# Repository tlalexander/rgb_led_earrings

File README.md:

# rgb_led_earrings

CAD:
https://cad.onshape.com/documents/09024334f2a397aa5bc58e5a/w/46f4970e419c9b5834fa8bd0/e/3dd3a53ca6818e1934df52f5

A gentle glow shines from your direction.
A twist, a step, a shimmy.
You move with freedom in your space.
Today is a good day. <3

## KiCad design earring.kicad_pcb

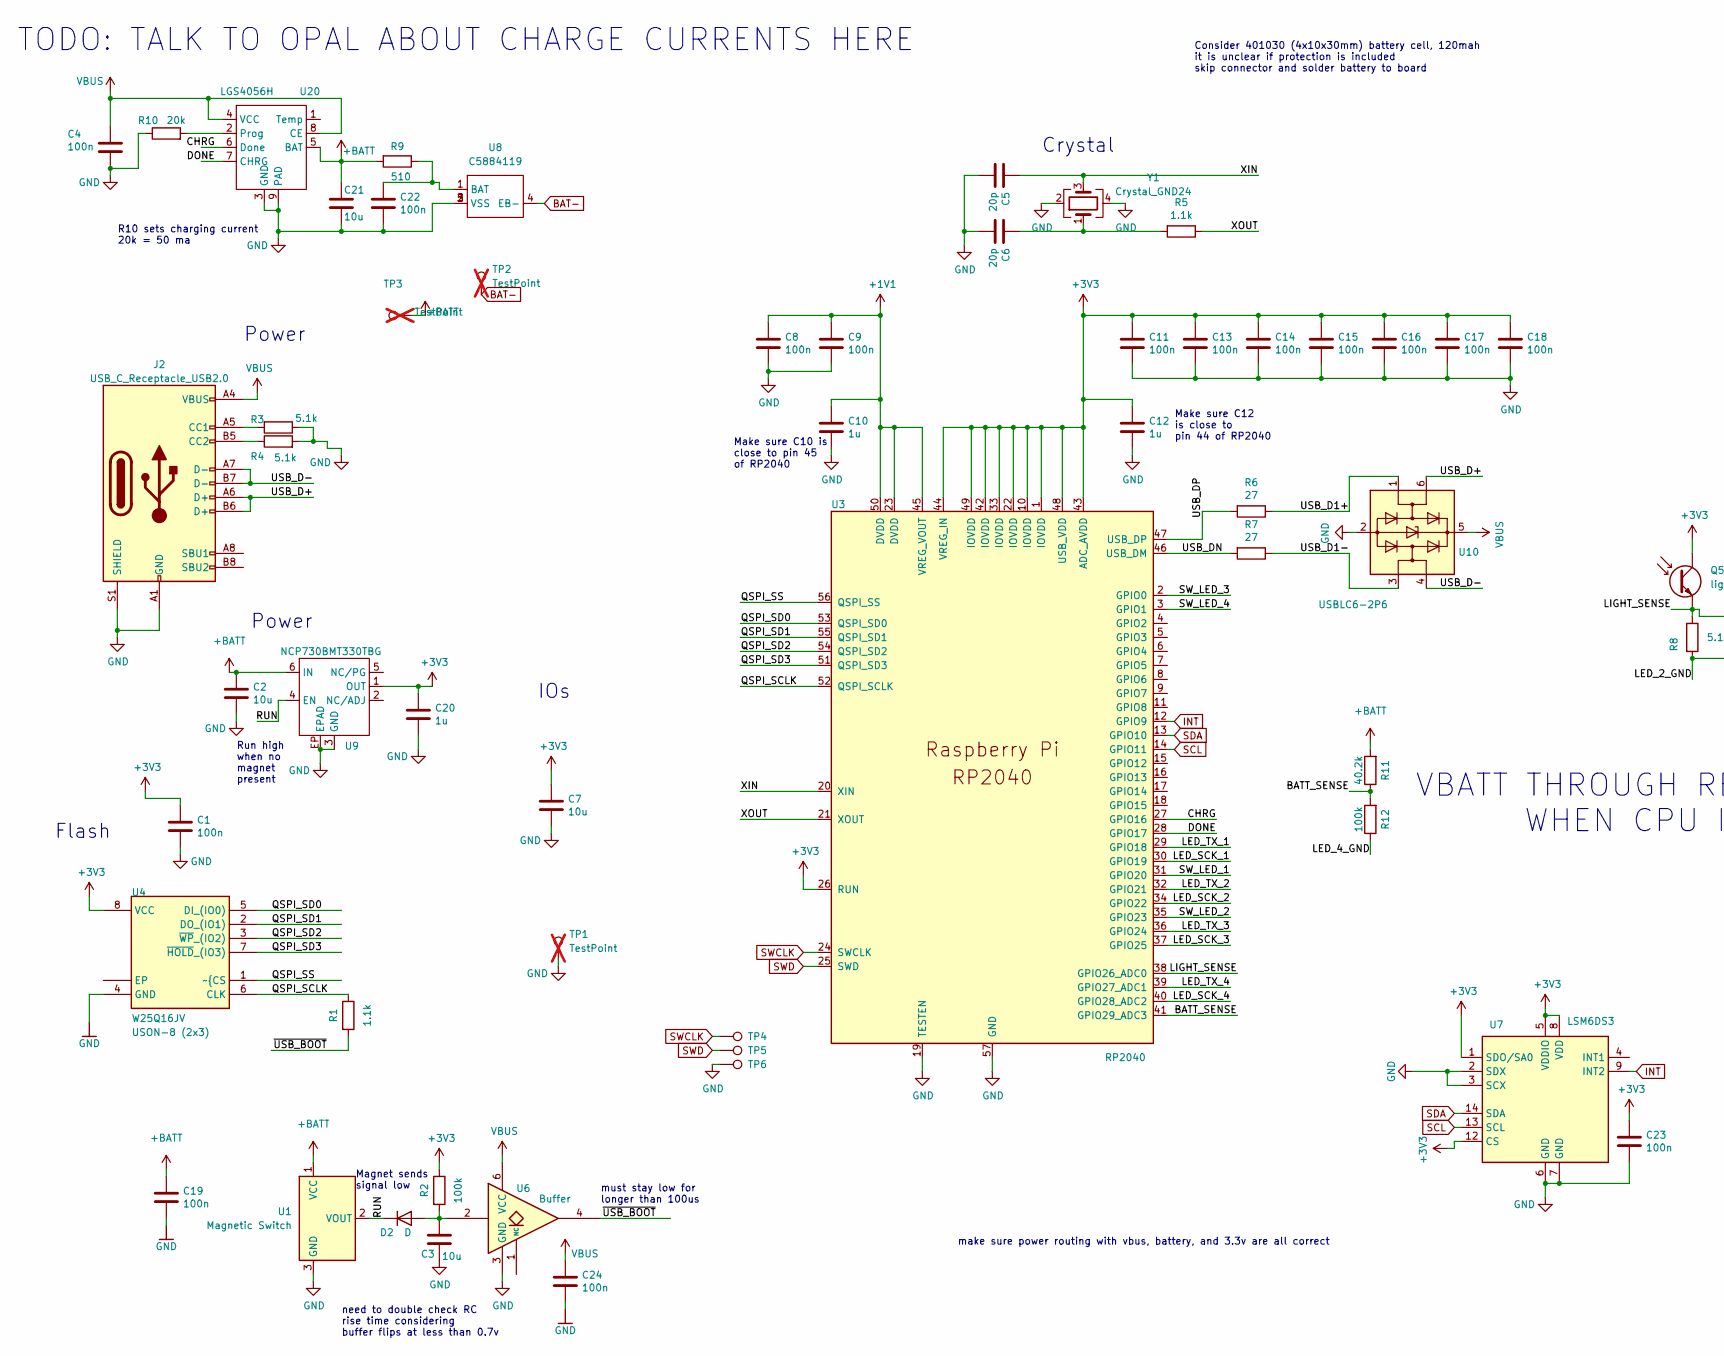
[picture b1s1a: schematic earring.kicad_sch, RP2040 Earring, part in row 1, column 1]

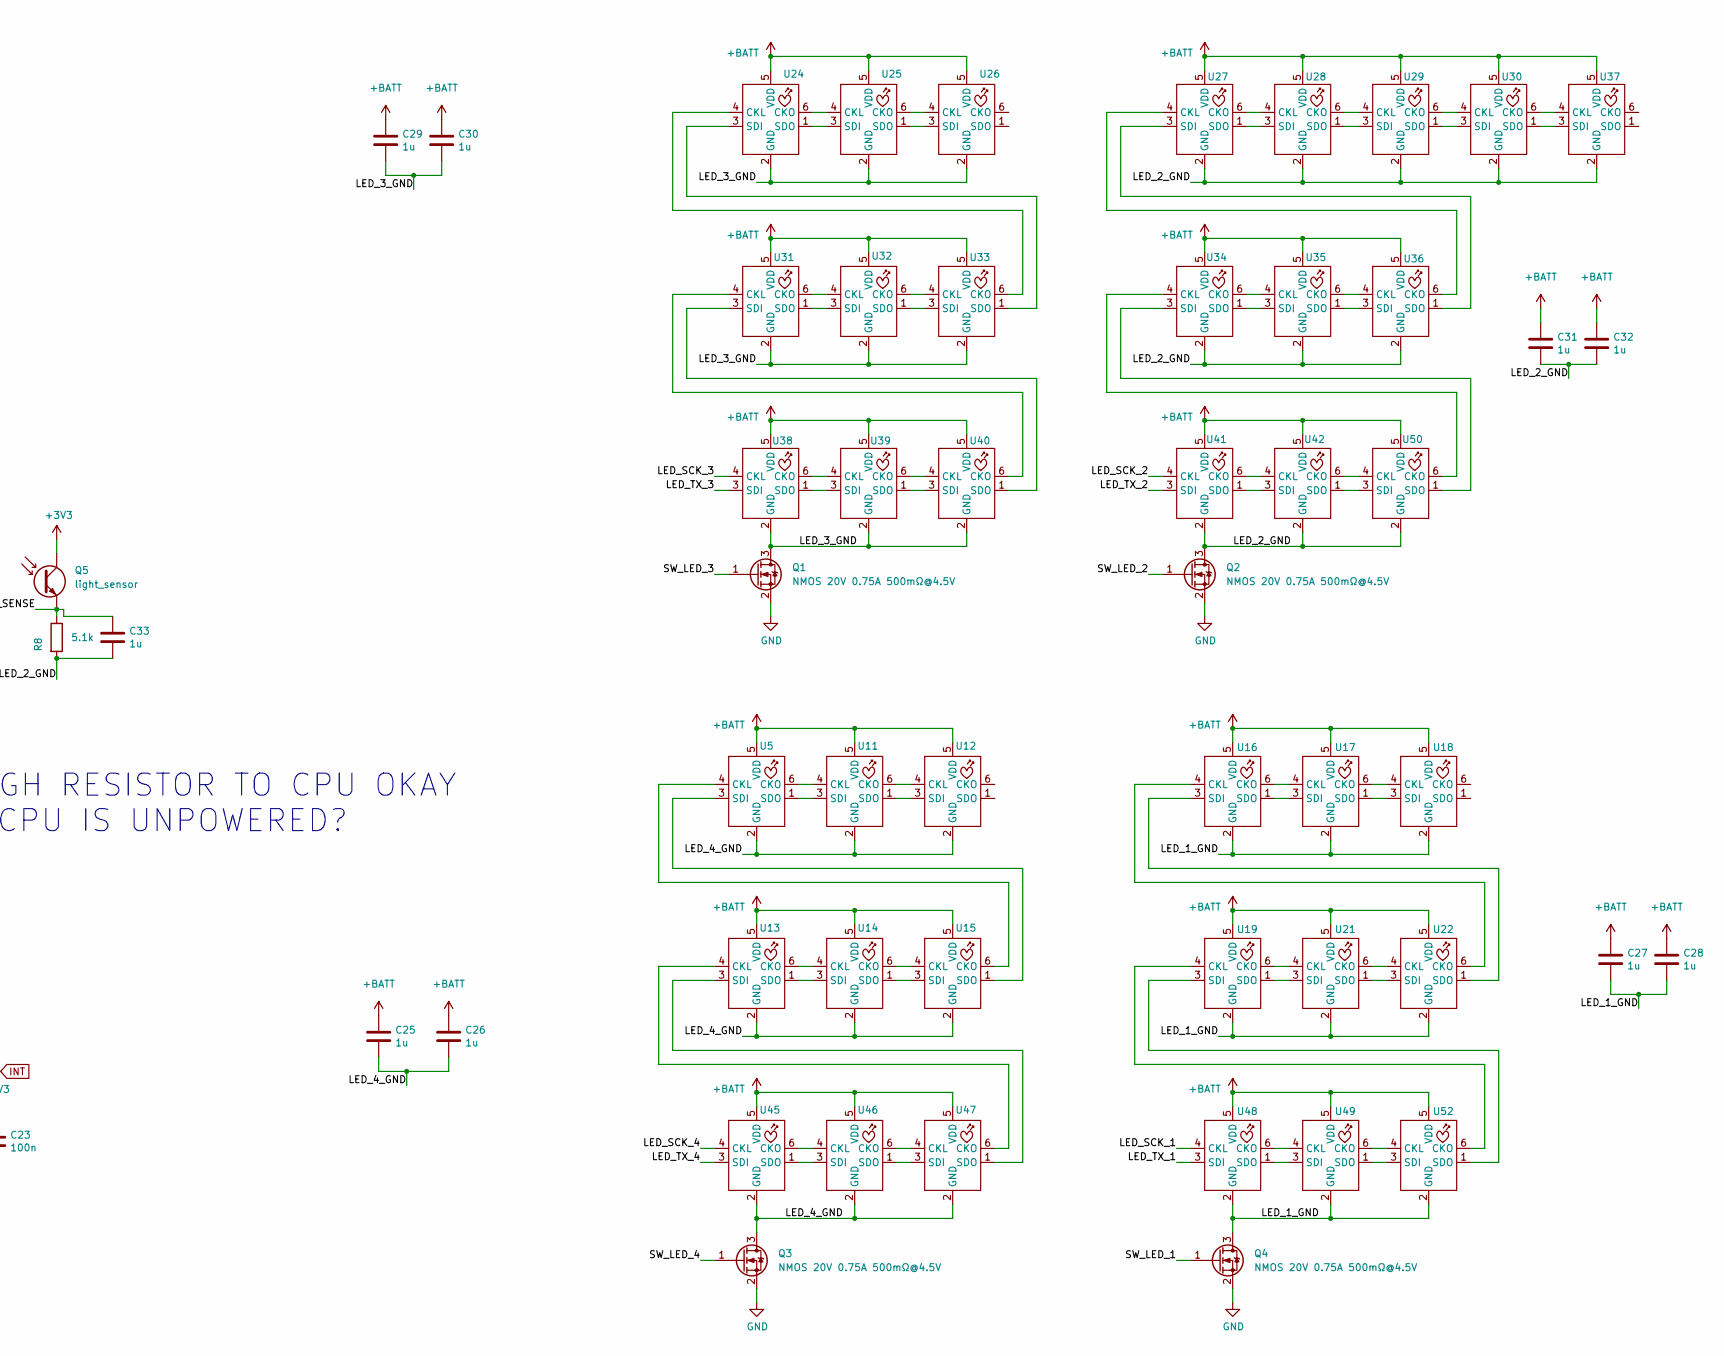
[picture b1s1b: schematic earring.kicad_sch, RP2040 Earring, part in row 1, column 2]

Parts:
C1, C4, C8, C9, C11, C13, C14, C15, C16, C17, C18, C19, C22, C23, C24: 100n; C_0402_1005Metric; LCSC C60474
C2, C3, C7, C21: 10u; C_0402_1005Metric; LCSC C315248
C5, C6: 20p; C_0402_1005Metric; LCSC C107000
C10, C12, C20, C25, C26, C27, C28, C29, C30, C31, C32, C33: 1u; C_0402_1005Metric; LCSC C29266
D2: D; D_SOD-523; LCSC C4468063
J2: USB_C_Receptacle_USB2.0; USB-C-TH_GT-USB-7055; LCSC C2686963
Q1, Q2, Q3, Q4: NMOS 20V 0.75A 500mΩ@4.5V; Diodes_DFN1006-3; LCSC C504098
Q5: light_sensor; LED_0603_1608Metric; LCSC C146233
R1, R5: 1.1k; R_0402_1005Metric; LCSC C325543
R2, R12: 100k; R_0402_1005Metric; LCSC C60491
R3, R4, R8: 5.1k; R_0402_1005Metric; LCSC C25905
R6, R7: 27; R_0402_1005Metric; LCSC C138021
R9: 510; R_0402_1005Metric; LCSC C137860
R10: 20k; R_0402_1005Metric; LCSC C25765
R11: 40.2k; R_0402_1005Metric; LCSC C25893
TP1: TestPoint; TestPoint_Pad_D1.0mm; LCSC C238130; not fitted
TP2, TP3: TestPoint; TestPoint_Pad_2.0x2.0mm; LCSC C238130; not fitted
TP4, TP5, TP6: TestPoint; TestPoint_Pad_1.0x1.0mm
U1: Magnetic Switch; DFN1608-3_L1.5-W0.8-P0.42-BL-EP; LCSC C879626
U3: RP2040; RP2040-QFN-56; LCSC C2040
U4: W25Q16JV; IC_W25Q16JVUXIQ_TR; MPN W25Q16JVUXIQ; LCSC C2843335
U5, U11, U12, U13, U14, U15, U16, U17, U18, U19, U21, U22, U25, U26, U27, U28, U29, U30, U31, U32, U33, U34, U35, U36, U37, U38, U39, U40, U41, U42, U45, U46, U47, U48, U49, U50, U52: LED-SK9822-EC20
U6: Buffer; UFDFN-6_1.45x1mm; LCSC C2864615
U7: LSM6DS3; LGA-14_3x2.5mm_P0.5mm_LayoutBorder3x4y; LCSC C2829074
U8: DFN1x1; LCSC C5884119
U9: NCP730BMT330TBG; WDFN-6-2x2; LCSC C892821
U10: USBLC6-2P6; SOT-666; LCSC C2827693
U20: LGS4056H; DFN-8-1EP_2x2mm_P0.5mm_EP0.9x1.5mm; LCSC C5124109
U24: SK9822-EC20; LED-SK9822-EC20
Y1: Crystal_GND24; Crystal_SMD_2520-4Pin_2.5x2.0mm; LCSC C284155

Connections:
+1V1: C8.1, C9.1, C10.1, U3.23 (DVDD), U3.45 (VREG_VOUT), U3.50 (DVDD)
+3V3: C1.1, C7.1, C11.1, C12.1, C13.1, C14.1, C15.1, C16.1, C17.1, C18.1, C20.1, C23.1, Q5.1, R2.1, U3.1 (IOVDD), U3.10 (IOVDD), U3.22 (IOVDD), U3.26 (RUN), U3.33 (IOVDD), U3.42 (IOVDD), U3.43 (ADC_AVDD), U3.44 (VREG_IN), U3.48 (USB_VDD), U3.49 (IOVDD), U4.8 (VCC), U7.1 (SDO/SA0), U7.5 (VDDIO), U7.8 (VDD), U7.12 (CS), U9.1 (OUT)
+BATT: C2.1, C19.1, C21.1, C25.1, C26.1, C27.1, C28.1, C29.1, C30.1, C31.1, C32.1, R9.2, R11.2, TP3.1, U1.1 (VCC), U5.5 (VDD), U9.6 (IN), U11.5 (VDD), U12.5 (VDD), U13.5 (VDD), U14.5 (VDD), U15.5 (VDD), U16.5 (VDD), U17.5 (VDD), U18.5 (VDD), U19.5 (VDD), U20.5 (BAT), U21.5 (VDD), U22.5 (VDD), U24.5 (VDD), U25.5 (VDD), U26.5 (VDD), U27.5 (VDD), U28.5 (VDD), U29.5 (VDD), U30.5 (VDD), U31.5 (VDD), U32.5 (VDD), U33.5 (VDD), U34.5 (VDD), U35.5 (VDD), U36.5 (VDD), U37.5 (VDD), U38.5 (VDD), U39.5 (VDD), U40.5 (VDD), U41.5 (VDD), U42.5 (VDD), U45.5 (VDD), U46.5 (VDD), U47.5 (VDD), U48.5 (VDD), U49.5 (VDD), U50.5 (VDD), U52.5 (VDD)
/BATT_SENSE: R11.1, R12.2, U3.41 (GPIO29_ADC3)
/CHRG: U3.27 (GPIO16), U20.6 (Done)
/DONE: U3.28 (GPIO17), U20.7 (CHRG)
/LED_1_GND: C27.2, C28.2, Q4.3 (D), U16.2 (GND), U17.2 (GND), U18.2 (GND), U19.2 (GND), U21.2 (GND), U22.2 (GND), U48.2 (GND), U49.2 (GND), U52.2 (GND)
/LED_2_GND: C31.2, C32.2, C33.2, Q2.3 (D), R8.2, U27.2 (GND), U28.2 (GND), U29.2 (GND), U30.2 (GND), U34.2 (GND), U35.2 (GND), U36.2 (GND), U37.2 (GND), U41.2 (GND), U42.2 (GND), U50.2 (GND)
/LED_3_GND: C29.2, C30.2, Q1.3 (D), U24.2 (GND), U25.2 (GND), U26.2 (GND), U31.2 (GND), U32.2 (GND), U33.2 (GND), U38.2 (GND), U39.2 (GND), U40.2 (GND)
/LED_4_GND: C25.2, C26.2, Q3.3 (D), R12.1, U5.2 (GND), U11.2 (GND), U12.2 (GND), U13.2 (GND), U14.2 (GND), U15.2 (GND), U45.2 (GND), U46.2 (GND), U47.2 (GND)
/LED_SCK_1: U3.30 (GPIO19), U48.4 (CKL)
/LED_SCK_2: U3.34 (GPIO22), U41.4 (CKL)
/LED_SCK_3: U3.37 (GPIO25), U38.4 (CKL)
/LED_SCK_4: U3.40 (GPIO28_ADC2), U45.4 (CKL)
/LED_TX_1: U3.29 (GPIO18), U48.3 (SDI)
/LED_TX_2: U3.32 (GPIO21), U41.3 (SDI)
/LED_TX_3: U3.36 (GPIO24), U38.3 (SDI)
/LED_TX_4: U3.39 (GPIO27_ADC1), U45.3 (SDI)
/LIGHT_SENSE: C33.1, Q5.2, R8.1, U3.38 (GPIO26_ADC0)
/QSPI_SCLK: R1.1, U3.52 (QSPI_SCLK), U4.6 (CLK)
/QSPI_SD0: U3.53 (QSPI_SD0), U4.5 (DI_(IO0))
/QSPI_SD1: U3.55 (QSPI_SD1), U4.2 (DO_(IO1))
/QSPI_SD2: U3.54 (QSPI_SD2), U4.3 (~WP_(IO2))
/QSPI_SD3: U3.51 (QSPI_SD3), U4.7 (~HOLD_(IO3))
/QSPI_SS: U3.56 (QSPI_SS), U4.1 (~{CS)
/RUN: D2.1 (K), U1.2 (VOUT), U9.4 (EN)
/SW_LED_1: Q4.1 (G), U3.31 (GPIO20)
/SW_LED_2: Q2.1 (G), U3.35 (GPIO23)
/SW_LED_3: Q1.1 (G), U3.2 (GPIO0)
/SW_LED_4: Q3.1 (G), U3.3 (GPIO1)
/USB_D1+: R6.1, U10.1 (I/O1)
/USB_D1-: R7.1, U10.3 (I/O2)
/USB_D+: J2.A6 (D+), J2.B6 (D+), U10.6 (I/O1)
/USB_D-: J2.A7 (D-), J2.B7 (D-), U10.4 (I/O2)
/USB_DN: R7.2, U3.46 (USB_DM)
/USB_DP: R6.2, U3.47 (USB_DP)
/XIN: C5.1, U3.20 (XIN), Y1.3
/XOUT: R5.1, U3.21 (XOUT)
/~USB_BOOT: R1.2, U6.4
BAT-: TP2.1, U8.4 (EB-)
GND: C1.2, C2.2, C3.2, C4.2, C5.2, C6.2, C7.2, C8.2, C9.2, C10.2, C11.2, C12.2, C13.2, C14.2, C15.2, C16.2, C17.2, C18.2, C19.2, C20.2, C21.2, C22.2, C23.2, C24.2, J2.A1 (GND), J2.A12 (GND), J2.B1 (GND), J2.B12 (GND), J2.S1 (SHIELD), Q1.2 (S), Q2.2 (S), Q3.2 (S), Q4.2 (S), R3.1, R4.2, R10.1, TP1.1, TP6.1, U1.3 (GND), U3.19 (TESTEN), U3.57 (GND), U4.4 (GND), U6.3 (GND), U7.2 (SDX), U7.3 (SCX), U7.6 (GND), U7.7 (GND), U8.2 (VSS), U8.3 (VSS), U8.5 (VSS), U9.3 (GND), U9.EP (EPAD), U10.2 (GND), U20.3 (GND), U20.9 (PAD), Y1.2, Y1.4
INT: U3.12 (GPIO9), U7.9 (INT2)
unnamed: C6.1, R5.2, Y1.1
unnamed: C3.1, D2.2 (A), R2.2, U6.2
unnamed: J2.A5 (CC1), R3.2
unnamed: J2.B5 (CC2), R4.1
unnamed: C22.1, R9.1, U8.1 (BAT)
unnamed: U5.6 (CKO), U11.4 (CKL)
unnamed: U11.6 (CKO), U12.4 (CKL)
unnamed: U5.1 (SDO), U11.3 (SDI)
unnamed: U11.1 (SDO), U12.3 (SDI)
unnamed: U13.4 (CKL), U47.6 (CKO)
unnamed: U13.6 (CKO), U14.4 (CKL)
unnamed: U13.3 (SDI), U47.1 (SDO)
unnamed: U13.1 (SDO), U14.3 (SDI)
unnamed: U14.6 (CKO), U15.4 (CKL)
unnamed: U14.1 (SDO), U15.3 (SDI)
unnamed: U5.4 (CKL), U15.6 (CKO)
unnamed: U5.3 (SDI), U15.1 (SDO)
unnamed: U16.4 (CKL), U22.6 (CKO)
unnamed: U16.6 (CKO), U17.4 (CKL)
unnamed: U16.3 (SDI), U22.1 (SDO)
unnamed: U16.1 (SDO), U17.3 (SDI)
unnamed: U17.6 (CKO), U18.4 (CKL)
unnamed: U17.1 (SDO), U18.3 (SDI)
unnamed: U19.4 (CKL), U52.6 (CKO)
unnamed: U19.6 (CKO), U21.4 (CKL)
unnamed: U19.3 (SDI), U52.1 (SDO)
unnamed: U19.1 (SDO), U21.3 (SDI)
unnamed: R10.2, U20.2 (Prog)
unnamed: U21.6 (CKO), U22.4 (CKL)
unnamed: U21.1 (SDO), U22.3 (SDI)
unnamed: U24.4 (CKL), U33.6 (CKO)
unnamed: U24.6 (CKO), U25.4 (CKL)
unnamed: U24.3 (SDI), U33.1 (SDO)
unnamed: U24.1 (SDO), U25.3 (SDI)
unnamed: U25.6 (CKO), U26.4 (CKL)
unnamed: U25.1 (SDO), U26.3 (SDI)
unnamed: U27.4 (CKL), U36.6 (CKO)
unnamed: U27.6 (CKO), U28.4 (CKL)
unnamed: U27.3 (SDI), U36.1 (SDO)
unnamed: U27.1 (SDO), U28.3 (SDI)
unnamed: U28.6 (CKO), U29.4 (CKL)
unnamed: U28.1 (SDO), U29.3 (SDI)
unnamed: U29.6 (CKO), U30.4 (CKL)
unnamed: U29.1 (SDO), U30.3 (SDI)
unnamed: U30.6 (CKO), U37.4 (CKL)
unnamed: U30.1 (SDO), U37.3 (SDI)
unnamed: U31.4 (CKL), U40.6 (CKO)
unnamed: U31.6 (CKO), U32.4 (CKL)
unnamed: U31.3 (SDI), U40.1 (SDO)
unnamed: U31.1 (SDO), U32.3 (SDI)
unnamed: U32.6 (CKO), U33.4 (CKL)
unnamed: U32.1 (SDO), U33.3 (SDI)
unnamed: U34.4 (CKL), U50.6 (CKO)
unnamed: U34.6 (CKO), U35.4 (CKL)
unnamed: U34.3 (SDI), U50.1 (SDO)
unnamed: U34.1 (SDO), U35.3 (SDI)
unnamed: U35.6 (CKO), U36.4 (CKL)
unnamed: U35.1 (SDO), U36.3 (SDI)
unnamed: U38.6 (CKO), U39.4 (CKL)
unnamed: U38.1 (SDO), U39.3 (SDI)
unnamed: U39.6 (CKO), U40.4 (CKL)
unnamed: U39.1 (SDO), U40.3 (SDI)
unnamed: U41.6 (CKO), U42.4 (CKL)
unnamed: U41.1 (SDO), U42.3 (SDI)
unnamed: U42.6 (CKO), U50.4 (CKL)
unnamed: U42.1 (SDO), U50.3 (SDI)
unnamed: U45.6 (CKO), U46.4 (CKL)
unnamed: U45.1 (SDO), U46.3 (SDI)
unnamed: U46.6 (CKO), U47.4 (CKL)
unnamed: U46.1 (SDO), U47.3 (SDI)
unnamed: U48.6 (CKO), U49.4 (CKL)
unnamed: U48.1 (SDO), U49.3 (SDI)
unnamed: U49.6 (CKO), U52.4 (CKL)
unnamed: U49.1 (SDO), U52.3 (SDI)
SCL: U3.14 (GPIO11), U7.13 (SCL)
SDA: U3.13 (GPIO10), U7.14 (SDA)
SWCLK: TP4.1, U3.24 (SWCLK)
SWD: TP5.1, U3.25 (SWD)
VBUS: C4.1, C24.1, J2.A4 (VBUS), J2.A9 (VBUS), J2.B4 (VBUS), J2.B9 (VBUS), U6.6 (VCC), U10.5 (VBUS), U20.4 (VCC), U20.8 (CE)

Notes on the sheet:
Make sure C10 is close to pin 45 of RP2040
Consider 401030 (4x10x30mm) battery cell, 120mah it is unclear if protection is included skip connector and solder battery to board
Power
Crystal
R10 sets charging current 20k = 50 ma
need to double check RC rise time considering buffer flips at less than 0.7v
IOs
TODO: TALK TO OPAL ABOUT CHARGE CURRENTS HERE
must stay low for longer than 100us
VBATT THROUGH RESISTOR TO CPU OKAY WHEN CPU IS UNPOWERED?
Magnet sends signal low
Make sure C12 is close to pin 44 of RP2040
make sure power routing with vbus, battery, and 3.3v are all correct
Run high when no magnet present
Flash

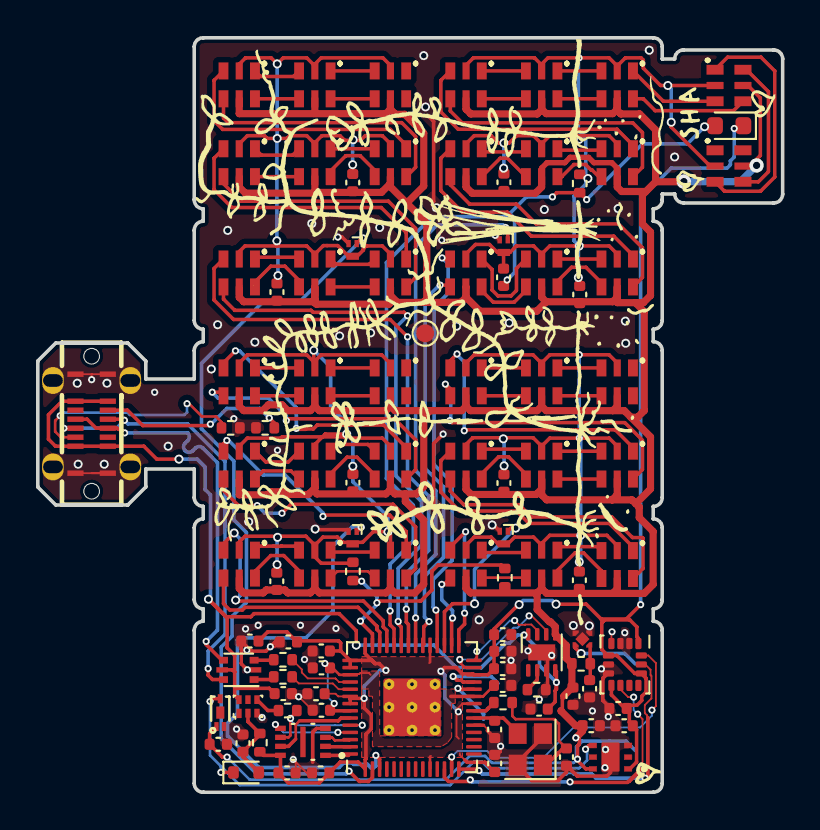
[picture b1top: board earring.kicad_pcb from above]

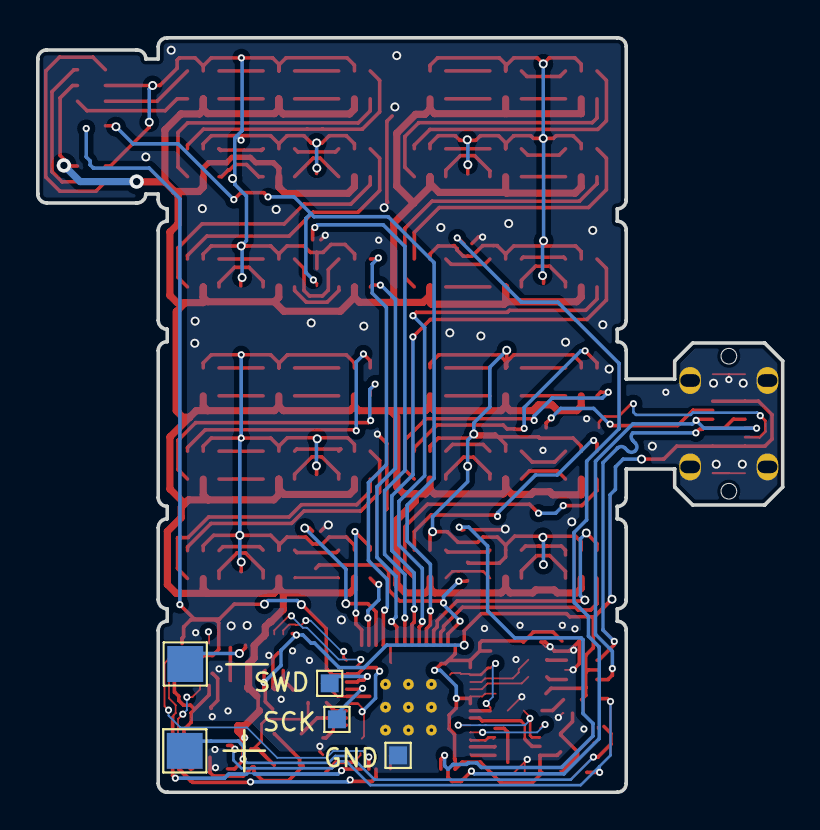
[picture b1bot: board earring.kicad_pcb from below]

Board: 2 copper layers, 41.4 x 41.9 mm, 106 parts (5 on the bottom side), 121 nets.

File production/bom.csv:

Designator,Footprint,Quantity,Value,LCSC Part #
"C1, C11, C13, C14, C15, C16, C17, C18, C19, C22, C23, C24, C4, C8, C9",0402,15,100n,C30926
"C10, C12, C20, C25, C26, C27, C28, C29, C30, C31, C32",0402,11,1u,C15849
"C2, C21, C3, C7",0402,4,10u,C15850
"C5, C6",0402,2,20p,C1648
D2,D_SOD-523,1,D,C4468063
J2,USB-C-TH_GT-USB-7055,1,USB_C_Receptacle_USB2.0,C2686963
"Q1, Q2, Q3, Q4",Diodes_DFN1006-3,4,NMOS 20V 0.75A 500mΩ@4.5V,C504098
"R1, R5",0402,2,1.1k,C325543
R10,0402,1,~,
R2,0402,1,100k,C60491
"R3, R4",0402,2,5.1k,C137955
"R6, R7",0402,2,27,C138021
R9,0402,1,510,C137860
U1,DFN1608-3_L1.5-W0.8-P0.42-BL-EP,1,Magnetic Switch,C879626
U10,SOT-666,1,USBLC6-2P6,C2827693
"U11, U12, U13, U14, U15, U16, U17, U18, U19, U21, U22, U24, U25, U26, U27, U28, U29, U30, U31, U32, U33, U34, U35, U36, U37, U38, U39, U40, U41, U42, U45, U46, U47, U48, U49, U5, U50, U52",LED-SK9822-EC20,38,~,
U20,DFN-8-1EP_2x2mm_P0.5mm_EP0.9x1.5mm,1,LGS4056H,C5124109
U3,RP2040-QFN-56,1,RP2040,C2040
U4,IC_W25Q16JVUXIQ_TR,1,W25Q16JV,C2843335
U6,UFDFN-6_1.45x1mm,1,Buffer,C7598681
U7,LGA-14_3x2.5mm_P0.5mm_LayoutBorder3x4y,1,LSM6DS3,C2829074
U8,DFN1x1,1,~,C5884119
U9,WDFN-6-2x2,1,~,
Y1,Crystal_SMD_2520-4Pin_2.5x2.0mm,1,Crystal_GND24,C284155

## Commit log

2024-02-05 Add image to readme
2024-02-07 Updated files, nearly complete. Added stiffener layer.
2024-05-25 Add light sensor, add more 3d models.
2024-05-25 Add license, update pics and readme.
2024-07-03 added silkscreen, debug contacts, and voltage monitoring
2024-07-30 update stiffener layer

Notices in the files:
earring.kicad_sch:
LICENSE: CERN-OHL-P
